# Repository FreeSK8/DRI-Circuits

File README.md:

# DRI-Circuits
Derelict Robot Industries Sandbox of various OS schematics &amp; board design files.

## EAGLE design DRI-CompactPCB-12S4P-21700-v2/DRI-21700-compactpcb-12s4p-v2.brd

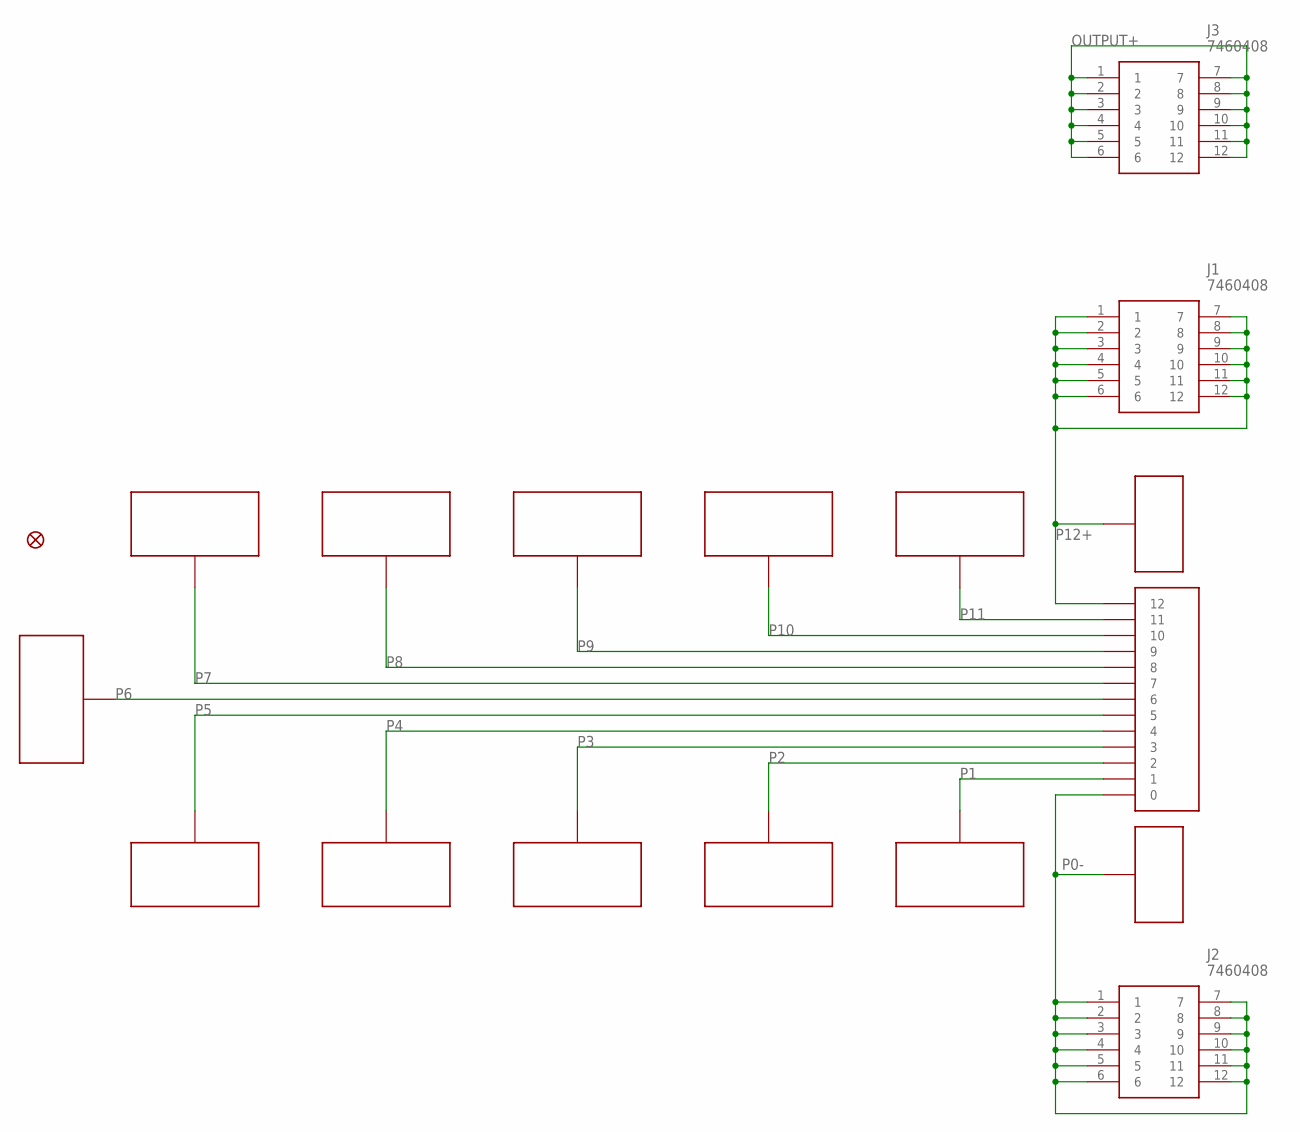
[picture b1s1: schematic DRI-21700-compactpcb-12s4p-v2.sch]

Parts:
FD2: FIDUCIAL1X2; FIDUCIAL-1X2
J1, J2, J3: 7460408
JP1: 13P-JST-2MM
P0: BUS-TERM-PAD-; TERM-PAD-
P1, P2, P3, P4, P5, P7, P8, P9, P10, P11: BAT-TERM-L
P6: BAT-TERM-END
P12: BUS-TERM-PAD+; TERM-PAD-

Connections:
OUTPUT+: J3.1, J3.2, J3.3, J3.4, J3.5, J3.6, J3.7, J3.8, J3.9, J3.10, J3.11, J3.12
P0-: J2.1, J2.2, J2.3, J2.4, J2.5, J2.6, J2.7, J2.8, J2.9, J2.10, J2.11, J2.12, JP1.P$1 (0), P0.P$3, P0.P$4, P0.P$5, P0.P$6, P0.P$7, P0.P$8, P0.P$9, P0.P$10, P0.P$11, P0.P$12, P0.P$13, P0.P$14, P0.P$15, P0.P$16, P0.P$17, P0.P$18, P0.P$19, P0.P$20, P0.P$21, P0.P$22, P0.P$23, P0.P$24, P0.P$25, P0.P$26, P0.P$27, P0.P$28, P0.P$29, P0.P$30, P0.P$31, P0.P$32, P0.P$33, P0.P$34, P0.P$35, P0.P$36, P0.P$37, P0.P$38, P0.P$39, P0.P$40, P0.P$41, P0.P$42, P0.P$43, P0.P$44, P0.P$45, P0.P$46, P0.P$47, P0.P$48, P0.P$49, P0.P$50, P0.P$51, P0.P$52, P0.P$53, P0.P$54, P0.P$55, P0.P$56, P0.P$57, P0.P$58, P0.P$59, P0.P$60, P0.P$61, P0.P$62, P0.P$63, P0.P$64, P0.P$65, P0.P$66, P0.P$67, P0.P$68, P0.P$69, P0.P$70, P0.P$71, P0.P$72, P0.P$73, P0.P$74, P0.P$75, P0.P$76, P0.P$77, P0.P$78, P0.P$79, P0.P$80, P0.P$81, P0.P$82, P0.P$83, P0.P$84, P0.P$85, P0.P$86, P0.P$87, P0.P$88, P0.P$89, P0.P$90, P0.P$91, P0.P$92, P0.P$93, P0.P$94, P0.P$95, P0.P$96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
P1: JP1.P$2 (1), P1.P$1, P1.P$2, P1.P$3, P1.P$4, P1.P$5, P1.P$6, P1.P$7, P1.P$8, P1.P$9, P1.P$10, P1.P$11, P1.P$12, P1.P$13, P1.P$14, P1.P$15, P1.P$16, P1.P$17, P1.P$18, P1.P$19, P1.P$20, P1.P$21, P1.P$22, P1.P$23, P1.P$24, P1.P$25, P1.P$26, P1.P$27, P1.P$28, P1.P$29, P1.P$30, P1.P$31, P1.P$32, P1.P$33, P1.P$34, P1.P$35, P1.P$36, P1.P$37, P1.P$38, P1.P$39, P1.P$40, P1.P$41, P1.P$42, P1.P$43, P1.P$44, P1.P$45, P1.P$46, P1.P$47, P1.P$48, P1.P$49, P1.P$50, P1.P$51, P1.P$52, P1.P$53, P1.P$54, P1.P$55, P1.P$56, P1.P$57, P1.P$58, P1.P$59, P1.P$60, P1.P$61, P1.P$62, P1.P$63, P1.P$64, P1.P$65, P1.P$66, P1.P$67, P1.P$68, P1.P$69, P1.P$70, P1.P$71, P1.P$72, P1.P$73, P1.P$74, P1.P$75, P1.P$76, P1.P$77, P1.P$78, P1.P$79, P1.P$80, P1.P$81, P1.P$82, P1.P$83, P1.P$84, P1.P$85, P1.P$86, P1.P$87, P1.P$88, P1.P$89, P1.P$90, P1.P$91, P1.P$92, P1.P$93, P1.P$94, P1.P$95, P1.P$96, P1.P$97, P1.P$98, P1.P$99, P1.P$100, P1.P$101, P1.P$102, P1.P$103, P1.P$104, P1.P$105, P1.P$106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
P2: JP1.P$3 (2), P2.P$1, P2.P$2, P2.P$3, P2.P$4, P2.P$5, P2.P$6, P2.P$7, P2.P$8, P2.P$9, P2.P$10, P2.P$11, P2.P$12, P2.P$13, P2.P$14, P2.P$15, P2.P$16, P2.P$17, P2.P$18, P2.P$19, P2.P$20, P2.P$21, P2.P$22, P2.P$23, P2.P$24, P2.P$25, P2.P$26, P2.P$27, P2.P$28, P2.P$29, P2.P$30, P2.P$31, P2.P$32, P2.P$33, P2.P$34, P2.P$35, P2.P$36, P2.P$37, P2.P$38, P2.P$39, P2.P$40, P2.P$41, P2.P$42, P2.P$43, P2.P$44, P2.P$45, P2.P$46, P2.P$47, P2.P$48, P2.P$49, P2.P$50, P2.P$51, P2.P$52, P2.P$53, P2.P$54, P2.P$55, P2.P$56, P2.P$57, P2.P$58, P2.P$59, P2.P$60, P2.P$61, P2.P$62, P2.P$63, P2.P$64, P2.P$65, P2.P$66, P2.P$67, P2.P$68, P2.P$69, P2.P$70, P2.P$71, P2.P$72, P2.P$73, P2.P$74, P2.P$75, P2.P$76, P2.P$77, P2.P$78, P2.P$79, P2.P$80, P2.P$81, P2.P$82, P2.P$83, P2.P$84, P2.P$85, P2.P$86, P2.P$87, P2.P$88, P2.P$89, P2.P$90, P2.P$91, P2.P$92, P2.P$93, P2.P$94, P2.P$95, P2.P$96, P2.P$97, P2.P$98, P2.P$99, P2.P$100, P2.P$101, P2.P$102, P2.P$103, P2.P$104, P2.P$105, P2.P$106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
P3: JP1.P$4 (3), P3.P$1, P3.P$2, P3.P$3, P3.P$4, P3.P$5, P3.P$6, P3.P$7, P3.P$8, P3.P$9, P3.P$10, P3.P$11, P3.P$12, P3.P$13, P3.P$14, P3.P$15, P3.P$16, P3.P$17, P3.P$18, P3.P$19, P3.P$20, P3.P$21, P3.P$22, P3.P$23, P3.P$24, P3.P$25, P3.P$26, P3.P$27, P3.P$28, P3.P$29, P3.P$30, P3.P$31, P3.P$32, P3.P$33, P3.P$34, P3.P$35, P3.P$36, P3.P$37, P3.P$38, P3.P$39, P3.P$40, P3.P$41, P3.P$42, P3.P$43, P3.P$44, P3.P$45, P3.P$46, P3.P$47, P3.P$48, P3.P$49, P3.P$50, P3.P$51, P3.P$52, P3.P$53, P3.P$54, P3.P$55, P3.P$56, P3.P$57, P3.P$58, P3.P$59, P3.P$60, P3.P$61, P3.P$62, P3.P$63, P3.P$64, P3.P$65, P3.P$66, P3.P$67, P3.P$68, P3.P$69, P3.P$70, P3.P$71, P3.P$72, P3.P$73, P3.P$74, P3.P$75, P3.P$76, P3.P$77, P3.P$78, P3.P$79, P3.P$80, P3.P$81, P3.P$82, P3.P$83, P3.P$84, P3.P$85, P3.P$86, P3.P$87, P3.P$88, P3.P$89, P3.P$90, P3.P$91, P3.P$92, P3.P$93, P3.P$94, P3.P$95, P3.P$96, P3.P$97, P3.P$98, P3.P$99, P3.P$100, P3.P$101, P3.P$102, P3.P$103, P3.P$104, P3.P$105, P3.P$106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
P4: JP1.P$5 (4), P4.P$1, P4.P$2, P4.P$3, P4.P$4, P4.P$5, P4.P$6, P4.P$7, P4.P$8, P4.P$9, P4.P$10, P4.P$11, P4.P$12, P4.P$13, P4.P$14, P4.P$15, P4.P$16, P4.P$17, P4.P$18, P4.P$19, P4.P$20, P4.P$21, P4.P$22, P4.P$23, P4.P$24, P4.P$25, P4.P$26, P4.P$27, P4.P$28, P4.P$29, P4.P$30, P4.P$31, P4.P$32, P4.P$33, P4.P$34, P4.P$35, P4.P$36, P4.P$37, P4.P$38, P4.P$39, P4.P$40, P4.P$41, P4.P$42, P4.P$43, P4.P$44, P4.P$45, P4.P$46, P4.P$47, P4.P$48, P4.P$49, P4.P$50, P4.P$51, P4.P$52, P4.P$53, P4.P$54, P4.P$55, P4.P$56, P4.P$57, P4.P$58, P4.P$59, P4.P$60, P4.P$61, P4.P$62, P4.P$63, P4.P$64, P4.P$65, P4.P$66, P4.P$67, P4.P$68, P4.P$69, P4.P$70, P4.P$71, P4.P$72, P4.P$73, P4.P$74, P4.P$75, P4.P$76, P4.P$77, P4.P$78, P4.P$79, P4.P$80, P4.P$81, P4.P$82, P4.P$83, P4.P$84, P4.P$85, P4.P$86, P4.P$87, P4.P$88, P4.P$89, P4.P$90, P4.P$91, P4.P$92, P4.P$93, P4.P$94, P4.P$95, P4.P$96, P4.P$97, P4.P$98, P4.P$99, P4.P$100, P4.P$101, P4.P$102, P4.P$103, P4.P$104, P4.P$105, P4.P$106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
P5: JP1.P$6 (5), P5.P$1, P5.P$2, P5.P$3, P5.P$4, P5.P$5, P5.P$6, P5.P$7, P5.P$8, P5.P$9, P5.P$10, P5.P$11, P5.P$12, P5.P$13, P5.P$14, P5.P$15, P5.P$16, P5.P$17, P5.P$18, P5.P$19, P5.P$20, P5.P$21, P5.P$22, P5.P$23, P5.P$24, P5.P$25, P5.P$26, P5.P$27, P5.P$28, P5.P$29, P5.P$30, P5.P$31, P5.P$32, P5.P$33, P5.P$34, P5.P$35, P5.P$36, P5.P$37, P5.P$38, P5.P$39, P5.P$40, P5.P$41, P5.P$42, P5.P$43, P5.P$44, P5.P$45, P5.P$46, P5.P$47, P5.P$48, P5.P$49, P5.P$50, P5.P$51, P5.P$52, P5.P$53, P5.P$54, P5.P$55, P5.P$56, P5.P$57, P5.P$58, P5.P$59, P5.P$60, P5.P$61, P5.P$62, P5.P$63, P5.P$64, P5.P$65, P5.P$66, P5.P$67, P5.P$68, P5.P$69, P5.P$70, P5.P$71, P5.P$72, P5.P$73, P5.P$74, P5.P$75, P5.P$76, P5.P$77, P5.P$78, P5.P$79, P5.P$80, P5.P$81, P5.P$82, P5.P$83, P5.P$84, P5.P$85, P5.P$86, P5.P$87, P5.P$88, P5.P$89, P5.P$90, P5.P$91, P5.P$92, P5.P$93, P5.P$94, P5.P$95, P5.P$96, P5.P$97, P5.P$98, P5.P$99, P5.P$100, P5.P$101, P5.P$102, P5.P$103, P5.P$104, P5.P$105, P5.P$106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
P6: JP1.P$7 (6), P6.P$1, P6.P$2, P6.P$3, P6.P$4, P6.P$5, P6.P$6, P6.P$7, P6.P$8, P6.P$9, P6.P$10, P6.P$11, P6.P$12, P6.P$13, P6.P$14, P6.P$15, P6.P$16, P6.P$17, P6.P$18, P6.P$19, P6.P$20, P6.P$21, P6.P$22, P6.P$23, P6.P$24, P6.P$25, P6.P$26, P6.P$27, P6.P$28, P6.P$29, P6.P$30, P6.P$31, P6.P$32, P6.P$33, P6.P$34, P6.P$35, P6.P$36, P6.P$37, P6.P$38, P6.P$39, P6.P$40, P6.P$41, P6.P$42, P6.P$43, P6.P$44, P6.P$45, P6.P$46, P6.P$47, P6.P$48, P6.P$49, P6.P$50, P6.P$51, P6.P$52, P6.P$53, P6.P$54, P6.P$55, P6.P$56, P6.P$57, P6.P$58, P6.P$59, P6.P$60, P6.P$61, P6.P$62, P6.P$63, P6.P$64, P6.P$65, P6.P$66, P6.P$67, P6.P$68, P6.P$69, P6.P$70, P6.P$71, P6.P$72, P6.P$73, P6.P$74, P6.P$75, P6.P$76, P6.P$77, P6.P$78, P6.P$79, P6.P$80, P6.P$81, P6.P$82, P6.P$83, P6.P$84, P6.P$85, P6.P$86, P6.P$87, P6.P$88, P6.P$89, P6.P$90, P6.P$91, P6.P$92, P6.P$93, P6.P$94, P6.P$95, P6.P$96, P6.P$97, P6.P$98, P6.P$99, P6.P$100, P6.P$101, P6.P$102, P6.P$103, P6.P$104, P6.P$105, P6.P$106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
P7: JP1.P$8 (7), P7.P$1, P7.P$2, P7.P$3, P7.P$4, P7.P$5, P7.P$6, P7.P$7, P7.P$8, P7.P$9, P7.P$10, P7.P$11, P7.P$12, P7.P$13, P7.P$14, P7.P$15, P7.P$16, P7.P$17, P7.P$18, P7.P$19, P7.P$20, P7.P$21, P7.P$22, P7.P$23, P7.P$24, P7.P$25, P7.P$26, P7.P$27, P7.P$28, P7.P$29, P7.P$30, P7.P$31, P7.P$32, P7.P$33, P7.P$34, P7.P$35, P7.P$36, P7.P$37, P7.P$38, P7.P$39, P7.P$40, P7.P$41, P7.P$42, P7.P$43, P7.P$44, P7.P$45, P7.P$46, P7.P$47, P7.P$48, P7.P$49, P7.P$50, P7.P$51, P7.P$52, P7.P$53, P7.P$54, P7.P$55, P7.P$56, P7.P$57, P7.P$58, P7.P$59, P7.P$60, P7.P$61, P7.P$62, P7.P$63, P7.P$64, P7.P$65, P7.P$66, P7.P$67, P7.P$68, P7.P$69, P7.P$70, P7.P$71, P7.P$72, P7.P$73, P7.P$74, P7.P$75, P7.P$76, P7.P$77, P7.P$78, P7.P$79, P7.P$80, P7.P$81, P7.P$82, P7.P$83, P7.P$84, P7.P$85, P7.P$86, P7.P$87, P7.P$88, P7.P$89, P7.P$90, P7.P$91, P7.P$92, P7.P$93, P7.P$94, P7.P$95, P7.P$96, P7.P$97, P7.P$98, P7.P$99, P7.P$100, P7.P$101, P7.P$102, P7.P$103, P7.P$104, P7.P$105, P7.P$106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
P8: JP1.P$9 (8), P8.P$1, P8.P$2, P8.P$3, P8.P$4, P8.P$5, P8.P$6, P8.P$7, P8.P$8, P8.P$9, P8.P$10, P8.P$11, P8.P$12, P8.P$13, P8.P$14, P8.P$15, P8.P$16, P8.P$17, P8.P$18, P8.P$19, P8.P$20, P8.P$21, P8.P$22, P8.P$23, P8.P$24, P8.P$25, P8.P$26, P8.P$27, P8.P$28, P8.P$29, P8.P$30, P8.P$31, P8.P$32, P8.P$33, P8.P$34, P8.P$35, P8.P$36, P8.P$37, P8.P$38, P8.P$39, P8.P$40, P8.P$41, P8.P$42, P8.P$43, P8.P$44, P8.P$45, P8.P$46, P8.P$47, P8.P$48, P8.P$49, P8.P$50, P8.P$51, P8.P$52, P8.P$53, P8.P$54, P8.P$55, P8.P$56, P8.P$57, P8.P$58, P8.P$59, P8.P$60, P8.P$61, P8.P$62, P8.P$63, P8.P$64, P8.P$65, P8.P$66, P8.P$67, P8.P$68, P8.P$69, P8.P$70, P8.P$71, P8.P$72, P8.P$73, P8.P$74, P8.P$75, P8.P$76, P8.P$77, P8.P$78, P8.P$79, P8.P$80, P8.P$81, P8.P$82, P8.P$83, P8.P$84, P8.P$85, P8.P$86, P8.P$87, P8.P$88, P8.P$89, P8.P$90, P8.P$91, P8.P$92, P8.P$93, P8.P$94, P8.P$95, P8.P$96, P8.P$97, P8.P$98, P8.P$99, P8.P$100, P8.P$101, P8.P$102, P8.P$103, P8.P$104, P8.P$105, P8.P$106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
P9: JP1.P$10 (9), P9.P$1, P9.P$2, P9.P$3, P9.P$4, P9.P$5, P9.P$6, P9.P$7, P9.P$8, P9.P$9, P9.P$10, P9.P$11, P9.P$12, P9.P$13, P9.P$14, P9.P$15, P9.P$16, P9.P$17, P9.P$18, P9.P$19, P9.P$20, P9.P$21, P9.P$22, P9.P$23, P9.P$24, P9.P$25, P9.P$26, P9.P$27, P9.P$28, P9.P$29, P9.P$30, P9.P$31, P9.P$32, P9.P$33, P9.P$34, P9.P$35, P9.P$36, P9.P$37, P9.P$38, P9.P$39, P9.P$40, P9.P$41, P9.P$42, P9.P$43, P9.P$44, P9.P$45, P9.P$46, P9.P$47, P9.P$48, P9.P$49, P9.P$50, P9.P$51, P9.P$52, P9.P$53, P9.P$54, P9.P$55, P9.P$56, P9.P$57, P9.P$58, P9.P$59, P9.P$60, P9.P$61, P9.P$62, P9.P$63, P9.P$64, P9.P$65, P9.P$66, P9.P$67, P9.P$68, P9.P$69, P9.P$70, P9.P$71, P9.P$72, P9.P$73, P9.P$74, P9.P$75, P9.P$76, P9.P$77, P9.P$78, P9.P$79, P9.P$80, P9.P$81, P9.P$82, P9.P$83, P9.P$84, P9.P$85, P9.P$86, P9.P$87, P9.P$88, P9.P$89, P9.P$90, P9.P$91, P9.P$92, P9.P$93, P9.P$94, P9.P$95, P9.P$96, P9.P$97, P9.P$98, P9.P$99, P9.P$100, P9.P$101, P9.P$102, P9.P$103, P9.P$104, P9.P$105, P9.P$106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
P10: JP1.P$11 (10), P10.P$1, P10.P$2, P10.P$3, P10.P$4, P10.P$5, P10.P$6, P10.P$7, P10.P$8, P10.P$9, P10.P$10, P10.P$11, P10.P$12, P10.P$13, P10.P$14, P10.P$15, P10.P$16, P10.P$17, P10.P$18, P10.P$19, P10.P$20, P10.P$21, P10.P$22, P10.P$23, P10.P$24, P10.P$25, P10.P$26, P10.P$27, P10.P$28, P10.P$29, P10.P$30, P10.P$31, P10.P$32, P10.P$33, P10.P$34, P10.P$35, P10.P$36, P10.P$37, P10.P$38, P10.P$39, P10.P$40, P10.P$41, P10.P$42, P10.P$43, P10.P$44, P10.P$45, P10.P$46, P10.P$47, P10.P$48, P10.P$49, P10.P$50, P10.P$51, P10.P$52, P10.P$53, P10.P$54, P10.P$55, P10.P$56, P10.P$57, P10.P$58, P10.P$59, P10.P$60, P10.P$61, P10.P$62, P10.P$63, P10.P$64, P10.P$65, P10.P$66, P10.P$67, P10.P$68, P10.P$69, P10.P$70, P10.P$71, P10.P$72, P10.P$73, P10.P$74, P10.P$75, P10.P$76, P10.P$77, P10.P$78, P10.P$79, P10.P$80, P10.P$81, P10.P$82, P10.P$83, P10.P$84, P10.P$85, P10.P$86, P10.P$87, P10.P$88, P10.P$89, P10.P$90, P10.P$91, P10.P$92, P10.P$93, P10.P$94, P10.P$95, P10.P$96, P10.P$97, P10.P$98, P10.P$99, P10.P$100, P10.P$101, P10.P$102, P10.P$103, P10.P$104, P10.P$105, P10.P$106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
P11: JP1.P$12 (11), P11.P$1, P11.P$2, P11.P$3, P11.P$4, P11.P$5, P11.P$6, P11.P$7, P11.P$8, P11.P$9, P11.P$10, P11.P$11, P11.P$12, P11.P$13, P11.P$14, P11.P$15, P11.P$16, P11.P$17, P11.P$18, P11.P$19, P11.P$20, P11.P$21, P11.P$22, P11.P$23, P11.P$24, P11.P$25, P11.P$26, P11.P$27, P11.P$28, P11.P$29, P11.P$30, P11.P$31, P11.P$32, P11.P$33, P11.P$34, P11.P$35, P11.P$36, P11.P$37, P11.P$38, P11.P$39, P11.P$40, P11.P$41, P11.P$42, P11.P$43, P11.P$44, P11.P$45, P11.P$46, P11.P$47, P11.P$48, P11.P$49, P11.P$50, P11.P$51, P11.P$52, P11.P$53, P11.P$54, P11.P$55, P11.P$56, P11.P$57, P11.P$58, P11.P$59, P11.P$60, P11.P$61, P11.P$62, P11.P$63, P11.P$64, P11.P$65, P11.P$66, P11.P$67, P11.P$68, P11.P$69, P11.P$70, P11.P$71, P11.P$72, P11.P$73, P11.P$74, P11.P$75, P11.P$76, P11.P$77, P11.P$78, P11.P$79, P11.P$80, P11.P$81, P11.P$82, P11.P$83, P11.P$84, P11.P$85, P11.P$86, P11.P$87, P11.P$88, P11.P$89, P11.P$90, P11.P$91, P11.P$92, P11.P$93, P11.P$94, P11.P$95, P11.P$96, P11.P$97, P11.P$98, P11.P$99, P11.P$100, P11.P$101, P11.P$102, P11.P$103, P11.P$104, P11.P$105, P11.P$106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
P12+: J1.1, J1.2, J1.3, J1.4, J1.5, J1.6, J1.7, J1.8, J1.9, J1.10, J1.11, J1.12, JP1.P$13 (12), P12.P$3, P12.P$4, P12.P$5, P12.P$6, P12.P$7, P12.P$8, P12.P$9, P12.P$10, P12.P$11, P12.P$12, P12.P$13, P12.P$14, P12.P$15, P12.P$16, P12.P$17, P12.P$18, P12.P$19, P12.P$20, P12.P$21, P12.P$22, P12.P$23, P12.P$24, P12.P$25, P12.P$26, P12.P$27, P12.P$28, P12.P$29, P12.P$30, P12.P$31, P12.P$32, P12.P$33, P12.P$34, P12.P$35, P12.P$36, P12.P$37, P12.P$38, P12.P$39, P12.P$40, P12.P$41, P12.P$42, P12.P$43, P12.P$44, P12.P$45, P12.P$46, P12.P$47, P12.P$48, P12.P$49, P12.P$50, P12.P$51, P12.P$52, P12.P$53, P12.P$54, P12.P$55, P12.P$56, P12.P$57, P12.P$58, P12.P$59, P12.P$60, P12.P$61, P12.P$62, P12.P$63, P12.P$64, P12.P$65, P12.P$66, P12.P$67, P12.P$68, P12.P$69, P12.P$70, P12.P$71, P12.P$72, P12.P$73, P12.P$74, P12.P$75, P12.P$76, P12.P$77, P12.P$78, P12.P$79, P12.P$80, P12.P$81, P12.P$82, P12.P$83, P12.P$84, P12.P$85, P12.P$86, P12.P$87, P12.P$88, P12.P$89, P12.P$90, P12.P$91, P12.P$92, P12.P$93, P12.P$94, P12.P$95, P12.P$96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

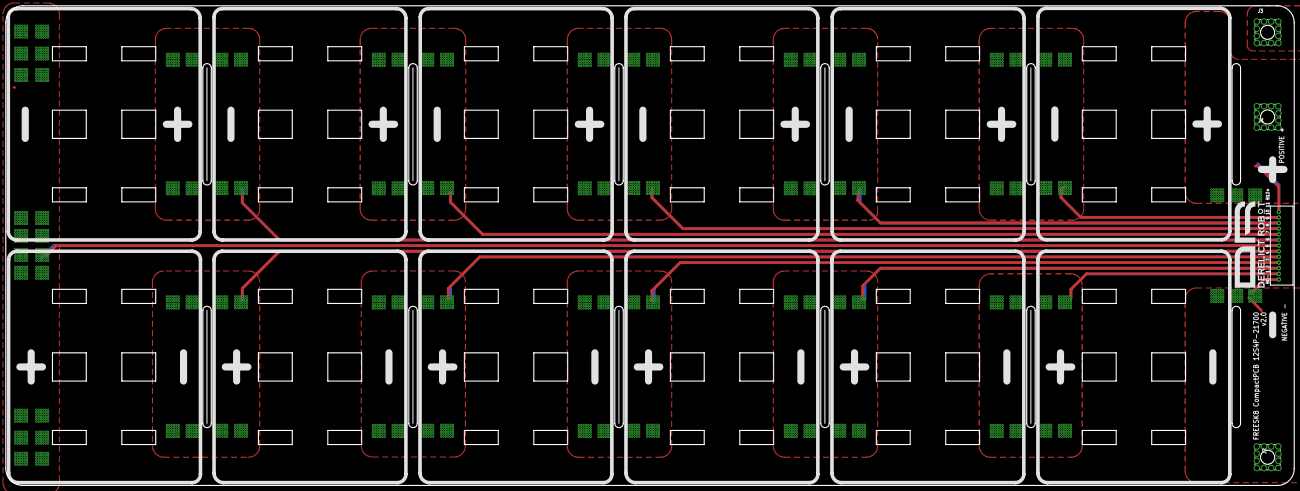
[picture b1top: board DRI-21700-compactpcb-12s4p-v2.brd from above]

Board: 2 copper layers, 456.6 x 170.0 mm, 30 parts (1 on the bottom side), 14 nets.

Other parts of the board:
U$1, U$2, U$3, U$4, U$5, U$6, U$7, U$8, U$9, U$10, U$11, U$12: 4PBATTERY

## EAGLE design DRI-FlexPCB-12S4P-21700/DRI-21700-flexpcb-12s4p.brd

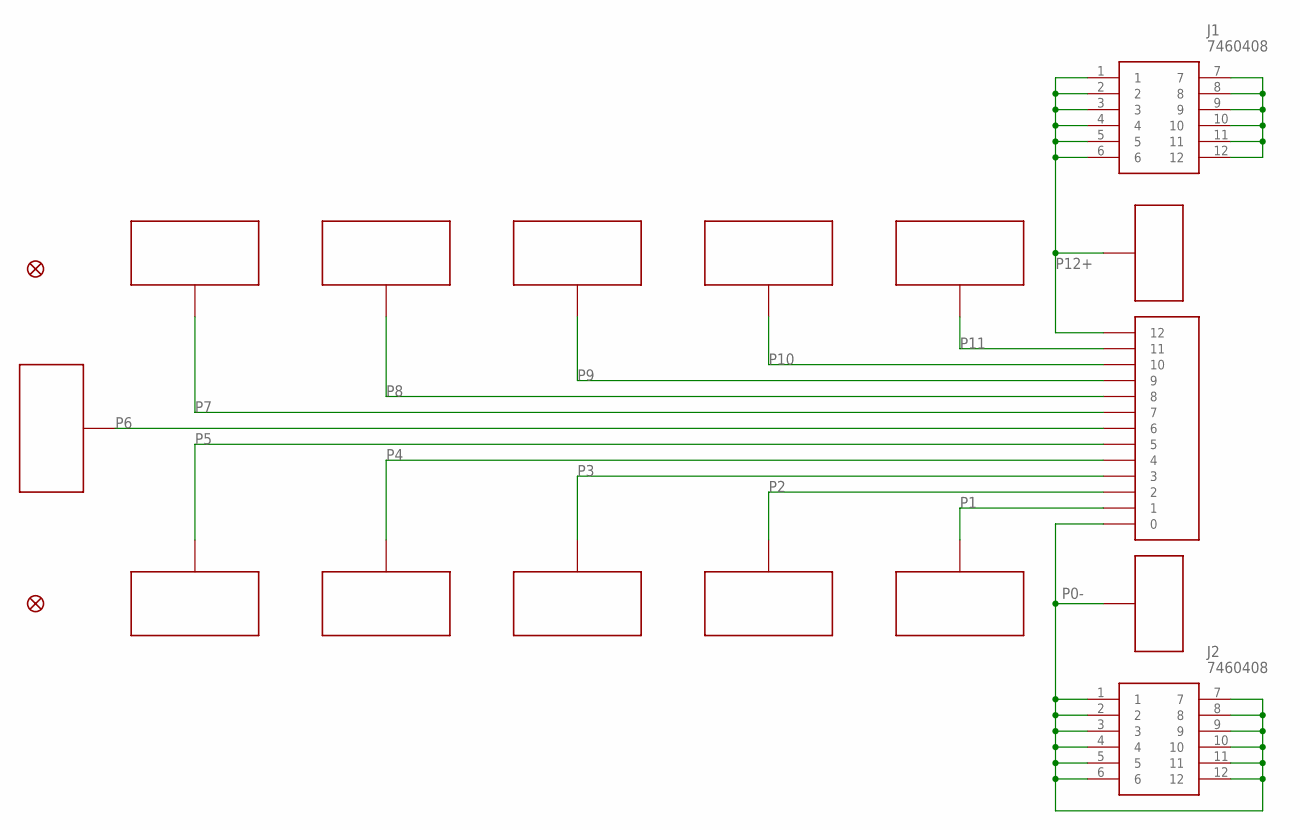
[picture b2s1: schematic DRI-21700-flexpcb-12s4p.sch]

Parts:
FD1, FD2: FIDUCIAL1X2; FIDUCIAL-1X2
J1, J2: 7460408
JP1: 13P-JST-2MM
P0, P12: BUS-TERM-PAD+; TERM-PAD-
P1, P3, P5, P7, P9, P11: BAT-TERM-L
P2, P4, P8, P10: BAT-TERM-M
P6: BAT-TERM-END

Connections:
unnamed: J1.7, J1.8, J1.9, J1.10, J1.11, J1.12
P0-: J2.1, J2.2, J2.3, J2.4, J2.5, J2.6, J2.7, J2.8, J2.9, J2.10, J2.11, J2.12, JP1.P$1 (0), P0.P$3, P0.P$4, P0.P$5, P0.P$6, P0.P$7, P0.P$8, P0.P$9, P0.P$10, P0.P$11, P0.P$12, P0.P$13, P0.P$14, P0.P$15, P0.P$16, P0.P$17, P0.P$18, P0.P$19, P0.P$20, P0.P$21, P0.P$22, P0.P$23, P0.P$24, P0.P$25, P0.P$26, P0.P$27, P0.P$28, P0.P$29, P0.P$30, P0.P$31, P0.P$32, P0.P$33, P0.P$34, P0.P$35, P0.P$36, P0.P$37, P0.P$38, P0.P$39, P0.P$40, P0.P$41, P0.P$42, P0.P$43, P0.P$44, P0.P$45, P0.P$46, P0.P$47, P0.P$48, P0.P$49, P0.P$50, P0.P$51, P0.P$52, P0.P$53, P0.P$54, P0.P$55, P0.P$56, P0.P$57, P0.P$58, P0.P$59, P0.P$60, P0.P$61, P0.P$62, P0.P$63, P0.P$64, P0.P$65, P0.P$66, P0.P$67, P0.P$68, P0.P$69, P0.P$70, P0.P$71, P0.P$72, P0.P$73, P0.P$74, P0.P$75, P0.P$76, P0.P$77, P0.P$78, P0.P$79, P0.P$80, P0.P$81, P0.P$82, P0.P$83, P0.P$84, P0.P$85, P0.P$86, P0.P$87, P0.P$88, P0.P$89, P0.P$90, P0.P$91, P0.P$92, P0.P$93, P0.P$94, P0.P$95, P0.P$96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
P1: JP1.P$2 (1), P1.P$5, P1.P$6, P1.P$7, P1.P$8, P1.P$9, P1.P$10, P1.P$11, P1.P$12, P1.P$13, P1.P$14, P1.P$15, P1.P$16, P1.P$17, P1.P$18, P1.P$19, P1.P$20, P1.P$21, P1.P$22, P1.P$23, P1.P$24, P1.P$25, P1.P$26, P1.P$27, P1.P$28, P1.P$29, P1.P$30, P1.P$31, P1.P$32, P1.P$33, P1.P$34, P1.P$35, P1.P$36, P1.P$37, P1.P$38, P1.P$39, P1.P$40, P1.P$41, P1.P$42, P1.P$43, P1.P$44, P1.P$45, P1.P$46, P1.P$47, P1.P$48, P1.P$49, P1.P$50, P1.P$51, P1.P$52, P1.P$53, P1.P$54, P1.P$55, P1.P$56, P1.P$57, P1.P$58, P1.P$59, P1.P$60, P1.P$61, P1.P$62, P1.P$63, P1.P$64, P1.P$65, P1.P$66, P1.P$67, P1.P$68, P1.P$69, P1.P$70, P1.P$71, P1.P$72, P1.P$73, P1.P$74, P1.P$75, P1.P$76, P1.P$77, P1.P$78, P1.P$79, P1.P$80, P1.P$81, P1.P$82, P1.P$83, P1.P$84, P1.P$85, P1.P$86, P1.P$87, P1.P$88, P1.P$89, P1.P$90, P1.P$91, P1.P$92, P1.P$93, P1.P$94, P1.P$95, P1.P$96, P1.P$97, P1.P$98, P1.P$99, P1.P$100, P1.P$101, P1.P$102, P1.P$103, P1.P$104, P1.P$105, P1.P$106, P1.P$107, P1.P$108, P1.P$109, P1.P$110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
P2: JP1.P$3 (2), P2.P$5, P2.P$6, P2.P$7, P2.P$8, P2.P$9, P2.P$10, P2.P$11, P2.P$12, P2.P$13, P2.P$14, P2.P$15, P2.P$16, P2.P$17, P2.P$18, P2.P$19, P2.P$20, P2.P$21, P2.P$22, P2.P$23, P2.P$24, P2.P$25, P2.P$26, P2.P$27, P2.P$28, P2.P$29, P2.P$30, P2.P$31, P2.P$32, P2.P$33, P2.P$34, P2.P$35, P2.P$36, P2.P$37, P2.P$38, P2.P$39, P2.P$40, P2.P$42, P2.P$43, P2.P$44, P2.P$45, P2.P$46, P2.P$47, P2.P$48, P2.P$49, P2.P$50, P2.P$51, P2.P$52, P2.P$53, P2.P$54, P2.P$55, P2.P$56, P2.P$57, P2.P$58, P2.P$59, P2.P$60, P2.P$61, P2.P$62, P2.P$63, P2.P$64, P2.P$65, P2.P$66, P2.P$67, P2.P$68, P2.P$69, P2.P$70, P2.P$71, P2.P$72, P2.P$73, P2.P$74, P2.P$75, P2.P$76, P2.P$77, P2.P$79, P2.P$80, P2.P$81, P2.P$82, P2.P$83, P2.P$84, P2.P$85, P2.P$86, P2.P$87, P2.P$88, P2.P$89, P2.P$90, P2.P$91, P2.P$92, P2.P$93, P2.P$94, P2.P$95, P2.P$96, P2.P$97, P2.P$98, P2.P$99, P2.P$100, P2.P$101, P2.P$102, P2.P$103, P2.P$104, P2.P$105, P2.P$106, P2.P$107, P2.P$108, P2.P$109, P2.P$110, P2.P$111, P2.P$112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
P3: JP1.P$4 (3), P3.P$5, P3.P$6, P3.P$7, P3.P$8, P3.P$9, P3.P$10, P3.P$11, P3.P$12, P3.P$13, P3.P$14, P3.P$15, P3.P$16, P3.P$17, P3.P$18, P3.P$19, P3.P$20, P3.P$21, P3.P$22, P3.P$23, P3.P$24, P3.P$25, P3.P$26, P3.P$27, P3.P$28, P3.P$29, P3.P$30, P3.P$31, P3.P$32, P3.P$33, P3.P$34, P3.P$35, P3.P$36, P3.P$37, P3.P$38, P3.P$39, P3.P$40, P3.P$41, P3.P$42, P3.P$43, P3.P$44, P3.P$45, P3.P$46, P3.P$47, P3.P$48, P3.P$49, P3.P$50, P3.P$51, P3.P$52, P3.P$53, P3.P$54, P3.P$55, P3.P$56, P3.P$57, P3.P$58, P3.P$59, P3.P$60, P3.P$61, P3.P$62, P3.P$63, P3.P$64, P3.P$65, P3.P$66, P3.P$67, P3.P$68, P3.P$69, P3.P$70, P3.P$71, P3.P$72, P3.P$73, P3.P$74, P3.P$75, P3.P$76, P3.P$77, P3.P$78, P3.P$79, P3.P$80, P3.P$81, P3.P$82, P3.P$83, P3.P$84, P3.P$85, P3.P$86, P3.P$87, P3.P$88, P3.P$89, P3.P$90, P3.P$91, P3.P$92, P3.P$93, P3.P$94, P3.P$95, P3.P$96, P3.P$97, P3.P$98, P3.P$99, P3.P$100, P3.P$101, P3.P$102, P3.P$103, P3.P$104, P3.P$105, P3.P$106, P3.P$107, P3.P$108, P3.P$109, P3.P$110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
P4: JP1.P$5 (4), P4.P$5, P4.P$6, P4.P$7, P4.P$8, P4.P$9, P4.P$10, P4.P$11, P4.P$12, P4.P$13, P4.P$14, P4.P$15, P4.P$16, P4.P$17, P4.P$18, P4.P$19, P4.P$20, P4.P$21, P4.P$22, P4.P$23, P4.P$24, P4.P$25, P4.P$26, P4.P$27, P4.P$28, P4.P$29, P4.P$30, P4.P$31, P4.P$32, P4.P$33, P4.P$34, P4.P$35, P4.P$36, P4.P$37, P4.P$38, P4.P$39, P4.P$40, P4.P$42, P4.P$43, P4.P$44, P4.P$45, P4.P$46, P4.P$47, P4.P$48, P4.P$49, P4.P$50, P4.P$51, P4.P$52, P4.P$53, P4.P$54, P4.P$55, P4.P$56, P4.P$57, P4.P$58, P4.P$59, P4.P$60, P4.P$61, P4.P$62, P4.P$63, P4.P$64, P4.P$65, P4.P$66, P4.P$67, P4.P$68, P4.P$69, P4.P$70, P4.P$71, P4.P$72, P4.P$73, P4.P$74, P4.P$75, P4.P$76, P4.P$77, P4.P$79, P4.P$80, P4.P$81, P4.P$82, P4.P$83, P4.P$84, P4.P$85, P4.P$86, P4.P$87, P4.P$88, P4.P$89, P4.P$90, P4.P$91, P4.P$92, P4.P$93, P4.P$94, P4.P$95, P4.P$96, P4.P$97, P4.P$98, P4.P$99, P4.P$100, P4.P$101, P4.P$102, P4.P$103, P4.P$104, P4.P$105, P4.P$106, P4.P$107, P4.P$108, P4.P$109, P4.P$110, P4.P$111, P4.P$112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
P5: JP1.P$6 (5), P5.P$5, P5.P$6, P5.P$7, P5.P$8, P5.P$9, P5.P$10, P5.P$11, P5.P$12, P5.P$13, P5.P$14, P5.P$15, P5.P$16, P5.P$17, P5.P$18, P5.P$19, P5.P$20, P5.P$21, P5.P$22, P5.P$23, P5.P$24, P5.P$25, P5.P$26, P5.P$27, P5.P$28, P5.P$29, P5.P$30, P5.P$31, P5.P$32, P5.P$33, P5.P$34, P5.P$35, P5.P$36, P5.P$37, P5.P$38, P5.P$39, P5.P$40, P5.P$41, P5.P$42, P5.P$43, P5.P$44, P5.P$45, P5.P$46, P5.P$47, P5.P$48, P5.P$49, P5.P$50, P5.P$51, P5.P$52, P5.P$53, P5.P$54, P5.P$55, P5.P$56, P5.P$57, P5.P$58, P5.P$59, P5.P$60, P5.P$61, P5.P$62, P5.P$63, P5.P$64, P5.P$65, P5.P$66, P5.P$67, P5.P$68, P5.P$69, P5.P$70, P5.P$71, P5.P$72, P5.P$73, P5.P$74, P5.P$75, P5.P$76, P5.P$77, P5.P$78, P5.P$79, P5.P$80, P5.P$81, P5.P$82, P5.P$83, P5.P$84, P5.P$85, P5.P$86, P5.P$87, P5.P$88, P5.P$89, P5.P$90, P5.P$91, P5.P$92, P5.P$93, P5.P$94, P5.P$95, P5.P$96, P5.P$97, P5.P$98, P5.P$99, P5.P$100, P5.P$101, P5.P$102, P5.P$103, P5.P$104, P5.P$105, P5.P$106, P5.P$107, P5.P$108, P5.P$109, P5.P$110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
P6: JP1.P$7 (6), P6.P$2, P6.P$3, P6.P$4, P6.P$5, P6.P$6, P6.P$7, P6.P$8, P6.P$9, P6.P$10, P6.P$11, P6.P$12, P6.P$13, P6.P$14, P6.P$15, P6.P$16, P6.P$17, P6.P$18, P6.P$19, P6.P$20, P6.P$21, P6.P$22, P6.P$23, P6.P$24, P6.P$25, P6.P$26, P6.P$27, P6.P$28, P6.P$29, P6.P$30, P6.P$31, P6.P$32, P6.P$33, P6.P$34, P6.P$35, P6.P$36, P6.P$37, P6.P$39, P6.P$40, P6.P$41, P6.P$42, P6.P$43, P6.P$44, P6.P$45, P6.P$46, P6.P$47, P6.P$48, P6.P$49, P6.P$50, P6.P$51, P6.P$52, P6.P$53, P6.P$54, P6.P$55, P6.P$56, P6.P$57, P6.P$58, P6.P$59, P6.P$60, P6.P$61, P6.P$62, P6.P$63, P6.P$64, P6.P$65, P6.P$66, P6.P$67, P6.P$68, P6.P$69, P6.P$70, P6.P$71, P6.P$72, P6.P$73, P6.P$74, P6.P$76, P6.P$77, P6.P$78, P6.P$79, P6.P$80, P6.P$81, P6.P$82, P6.P$83, P6.P$84, P6.P$85, P6.P$86, P6.P$87, P6.P$88, P6.P$89, P6.P$90, P6.P$91, P6.P$92, P6.P$93, P6.P$94, P6.P$95, P6.P$96, P6.P$97, P6.P$98, P6.P$99, P6.P$100, P6.P$101, P6.P$102, P6.P$103, P6.P$104, P6.P$105, P6.P$106, P6.P$107, P6.P$108, P6.P$109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
P7: JP1.P$8 (7), P7.P$5, P7.P$6, P7.P$7, P7.P$8, P7.P$9, P7.P$10, P7.P$11, P7.P$12, P7.P$13, P7.P$14, P7.P$15, P7.P$16, P7.P$17, P7.P$18, P7.P$19, P7.P$20, P7.P$21, P7.P$22, P7.P$23, P7.P$24, P7.P$25, P7.P$26, P7.P$27, P7.P$28, P7.P$29, P7.P$30, P7.P$31, P7.P$32, P7.P$33, P7.P$34, P7.P$35, P7.P$36, P7.P$37, P7.P$38, P7.P$39, P7.P$40, P7.P$41, P7.P$42, P7.P$43, P7.P$44, P7.P$45, P7.P$46, P7.P$47, P7.P$48, P7.P$49, P7.P$50, P7.P$51, P7.P$52, P7.P$53, P7.P$54, P7.P$55, P7.P$56, P7.P$57, P7.P$58, P7.P$59, P7.P$60, P7.P$61, P7.P$62, P7.P$63, P7.P$64, P7.P$65, P7.P$66, P7.P$67, P7.P$68, P7.P$69, P7.P$70, P7.P$71, P7.P$72, P7.P$73, P7.P$74, P7.P$75, P7.P$76, P7.P$77, P7.P$78, P7.P$79, P7.P$80, P7.P$81, P7.P$82, P7.P$83, P7.P$84, P7.P$85, P7.P$86, P7.P$87, P7.P$88, P7.P$89, P7.P$90, P7.P$91, P7.P$92, P7.P$93, P7.P$94, P7.P$95, P7.P$96, P7.P$97, P7.P$98, P7.P$99, P7.P$100, P7.P$101, P7.P$102, P7.P$103, P7.P$104, P7.P$105, P7.P$106, P7.P$107, P7.P$108, P7.P$109, P7.P$110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
P8: JP1.P$9 (8), P8.P$5, P8.P$6, P8.P$7, P8.P$8, P8.P$9, P8.P$10, P8.P$11, P8.P$12, P8.P$13, P8.P$14, P8.P$15, P8.P$16, P8.P$17, P8.P$18, P8.P$19, P8.P$20, P8.P$21, P8.P$22, P8.P$23, P8.P$24, P8.P$25, P8.P$26, P8.P$27, P8.P$28, P8.P$29, P8.P$30, P8.P$31, P8.P$32, P8.P$33, P8.P$34, P8.P$35, P8.P$36, P8.P$37, P8.P$38, P8.P$39, P8.P$40, P8.P$42, P8.P$43, P8.P$44, P8.P$45, P8.P$46, P8.P$47, P8.P$48, P8.P$49, P8.P$50, P8.P$51, P8.P$52, P8.P$53, P8.P$54, P8.P$55, P8.P$56, P8.P$57, P8.P$58, P8.P$59, P8.P$60, P8.P$61, P8.P$62, P8.P$63, P8.P$64, P8.P$65, P8.P$66, P8.P$67, P8.P$68, P8.P$69, P8.P$70, P8.P$71, P8.P$72, P8.P$73, P8.P$74, P8.P$75, P8.P$76, P8.P$77, P8.P$79, P8.P$80, P8.P$81, P8.P$82, P8.P$83, P8.P$84, P8.P$85, P8.P$86, P8.P$87, P8.P$88, P8.P$89, P8.P$90, P8.P$91, P8.P$92, P8.P$93, P8.P$94, P8.P$95, P8.P$96, P8.P$97, P8.P$98, P8.P$99, P8.P$100, P8.P$101, P8.P$102, P8.P$103, P8.P$104, P8.P$105, P8.P$106, P8.P$107, P8.P$108, P8.P$109, P8.P$110, P8.P$111, P8.P$112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
P9: JP1.P$10 (9), P9.P$5, P9.P$6, P9.P$7, P9.P$8, P9.P$9, P9.P$10, P9.P$11, P9.P$12, P9.P$13, P9.P$14, P9.P$15, P9.P$16, P9.P$17, P9.P$18, P9.P$19, P9.P$20, P9.P$21, P9.P$22, P9.P$23, P9.P$24, P9.P$25, P9.P$26, P9.P$27, P9.P$28, P9.P$29, P9.P$30, P9.P$31, P9.P$32, P9.P$33, P9.P$34, P9.P$35, P9.P$36, P9.P$37, P9.P$38, P9.P$39, P9.P$40, P9.P$41, P9.P$42, P9.P$43, P9.P$44, P9.P$45, P9.P$46, P9.P$47, P9.P$48, P9.P$49, P9.P$50, P9.P$51, P9.P$52, P9.P$53, P9.P$54, P9.P$55, P9.P$56, P9.P$57, P9.P$58, P9.P$59, P9.P$60, P9.P$61, P9.P$62, P9.P$63, P9.P$64, P9.P$65, P9.P$66, P9.P$67, P9.P$68, P9.P$69, P9.P$70, P9.P$71, P9.P$72, P9.P$73, P9.P$74, P9.P$75, P9.P$76, P9.P$77, P9.P$78, P9.P$79, P9.P$80, P9.P$81, P9.P$82, P9.P$83, P9.P$84, P9.P$85, P9.P$86, P9.P$87, P9.P$88, P9.P$89, P9.P$90, P9.P$91, P9.P$92, P9.P$93, P9.P$94, P9.P$95, P9.P$96, P9.P$97, P9.P$98, P9.P$99, P9.P$100, P9.P$101, P9.P$102, P9.P$103, P9.P$104, P9.P$105, P9.P$106, P9.P$107, P9.P$108, P9.P$109, P9.P$110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
P10: JP1.P$11 (10), P10.P$5, P10.P$6, P10.P$7, P10.P$8, P10.P$9, P10.P$10, P10.P$11, P10.P$12, P10.P$13, P10.P$14, P10.P$15, P10.P$16, P10.P$17, P10.P$18, P10.P$19, P10.P$20, P10.P$21, P10.P$22, P10.P$23, P10.P$24, P10.P$25, P10.P$26, P10.P$27, P10.P$28, P10.P$29, P10.P$30, P10.P$31, P10.P$32, P10.P$33, P10.P$34, P10.P$35, P10.P$36, P10.P$37, P10.P$38, P10.P$39, P10.P$40, P10.P$42, P10.P$43, P10.P$44, P10.P$45, P10.P$46, P10.P$47, P10.P$48, P10.P$49, P10.P$50, P10.P$51, P10.P$52, P10.P$53, P10.P$54, P10.P$55, P10.P$56, P10.P$57, P10.P$58, P10.P$59, P10.P$60, P10.P$61, P10.P$62, P10.P$63, P10.P$64, P10.P$65, P10.P$66, P10.P$67, P10.P$68, P10.P$69, P10.P$70, P10.P$71, P10.P$72, P10.P$73, P10.P$74, P10.P$75, P10.P$76, P10.P$77, P10.P$79, P10.P$80, P10.P$81, P10.P$82, P10.P$83, P10.P$84, P10.P$85, P10.P$86, P10.P$87, P10.P$88, P10.P$89, P10.P$90, P10.P$91, P10.P$92, P10.P$93, P10.P$94, P10.P$95, P10.P$96, P10.P$97, P10.P$98, P10.P$99, P10.P$100, P10.P$101, P10.P$102, P10.P$103, P10.P$104, P10.P$105, P10.P$106, P10.P$107, P10.P$108, P10.P$109, P10.P$110, P10.P$111, P10.P$112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
P11: JP1.P$12 (11), P11.P$5, P11.P$6, P11.P$7, P11.P$8, P11.P$9, P11.P$10, P11.P$11, P11.P$12, P11.P$13, P11.P$14, P11.P$15, P11.P$16, P11.P$17, P11.P$18, P11.P$19, P11.P$20, P11.P$21, P11.P$22, P11.P$23, P11.P$24, P11.P$25, P11.P$26, P11.P$27, P11.P$28, P11.P$29, P11.P$30, P11.P$31, P11.P$32, P11.P$33, P11.P$34, P11.P$35, P11.P$36, P11.P$37, P11.P$38, P11.P$39, P11.P$40, P11.P$41, P11.P$42, P11.P$43, P11.P$44, P11.P$45, P11.P$46, P11.P$47, P11.P$48, P11.P$49, P11.P$50, P11.P$51, P11.P$52, P11.P$53, P11.P$54, P11.P$55, P11.P$56, P11.P$57, P11.P$58, P11.P$59, P11.P$60, P11.P$61, P11.P$62, P11.P$63, P11.P$64, P11.P$65, P11.P$66, P11.P$67, P11.P$68, P11.P$69, P11.P$70, P11.P$71, P11.P$72, P11.P$73, P11.P$74, P11.P$75, P11.P$76, P11.P$77, P11.P$78, P11.P$79, P11.P$80, P11.P$81, P11.P$82, P11.P$83, P11.P$84, P11.P$85, P11.P$86, P11.P$87, P11.P$88, P11.P$89, P11.P$90, P11.P$91, P11.P$92, P11.P$93, P11.P$94, P11.P$95, P11.P$96, P11.P$97, P11.P$98, P11.P$99, P11.P$100, P11.P$101, P11.P$102, P11.P$103, P11.P$104, P11.P$105, P11.P$106, P11.P$107, P11.P$108, P11.P$109, P11.P$110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
P12+: J1.1, J1.2, J1.3, J1.4, J1.5, J1.6, JP1.P$13 (12), P12.P$3, P12.P$4, P12.P$5, P12.P$6, P12.P$7, P12.P$8, P12.P$9, P12.P$10, P12.P$11, P12.P$12, P12.P$13, P12.P$14, P12.P$15, P12.P$16, P12.P$17, P12.P$18, P12.P$19, P12.P$20, P12.P$21, P12.P$22, P12.P$23, P12.P$24, P12.P$25, P12.P$26, P12.P$27, P12.P$28, P12.P$29, P12.P$30, P12.P$31, P12.P$32, P12.P$33, P12.P$34, P12.P$35, P12.P$36, P12.P$37, P12.P$38, P12.P$39, P12.P$40, P12.P$41, P12.P$42, P12.P$43, P12.P$44, P12.P$45, P12.P$46, P12.P$47, P12.P$48, P12.P$49, P12.P$50, P12.P$51, P12.P$52, P12.P$53, P12.P$54, P12.P$55, P12.P$56, P12.P$57, P12.P$58, P12.P$59, P12.P$60, P12.P$61, P12.P$62, P12.P$63, P12.P$64, P12.P$65, P12.P$66, P12.P$67, P12.P$68, P12.P$69, P12.P$70, P12.P$71, P12.P$72, P12.P$73, P12.P$74, P12.P$75, P12.P$76, P12.P$77, P12.P$78, P12.P$79, P12.P$80, P12.P$81, P12.P$82, P12.P$83, P12.P$84, P12.P$85, P12.P$86, P12.P$87, P12.P$88, P12.P$89, P12.P$90, P12.P$91, P12.P$92, P12.P$93, P12.P$94, P12.P$95, P12.P$96, P12.P$97, P12.P$98, P12.P$99, P12.P$100, P12.P$101, P12.P$102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

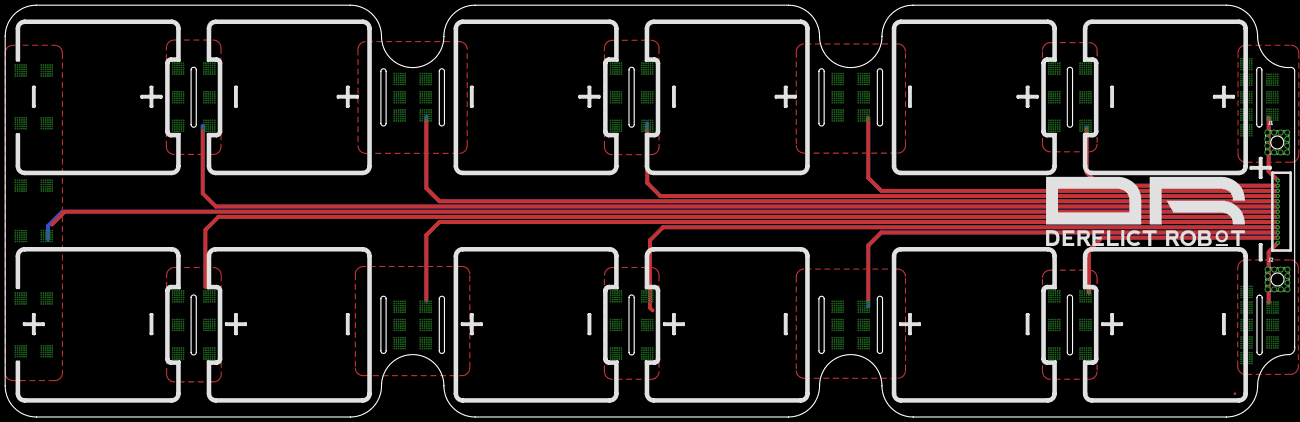
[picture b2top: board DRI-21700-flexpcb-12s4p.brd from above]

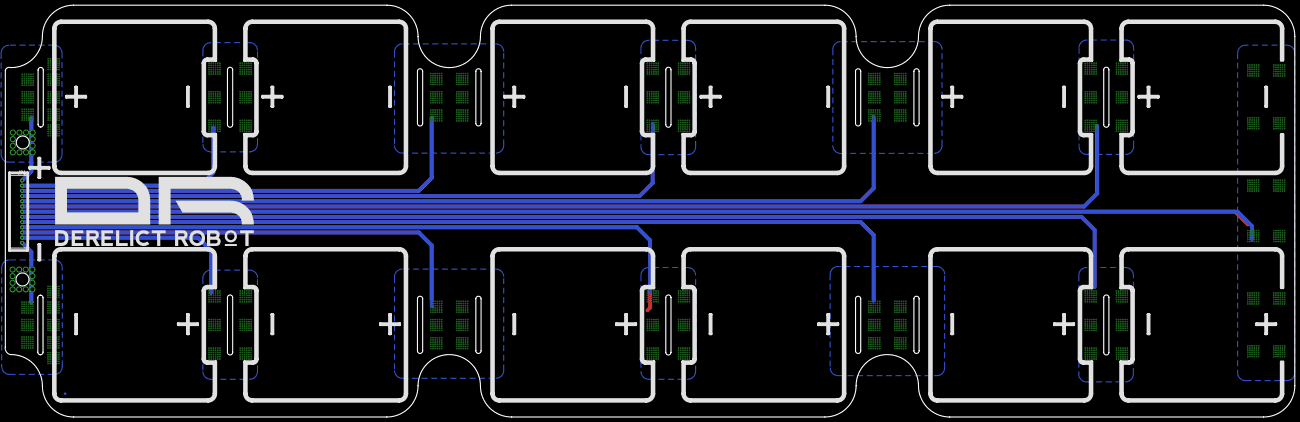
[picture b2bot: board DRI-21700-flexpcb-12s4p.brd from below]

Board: 2 copper layers, 496.0 x 158.4 mm, 18 parts (2 on the bottom side), 14 nets.

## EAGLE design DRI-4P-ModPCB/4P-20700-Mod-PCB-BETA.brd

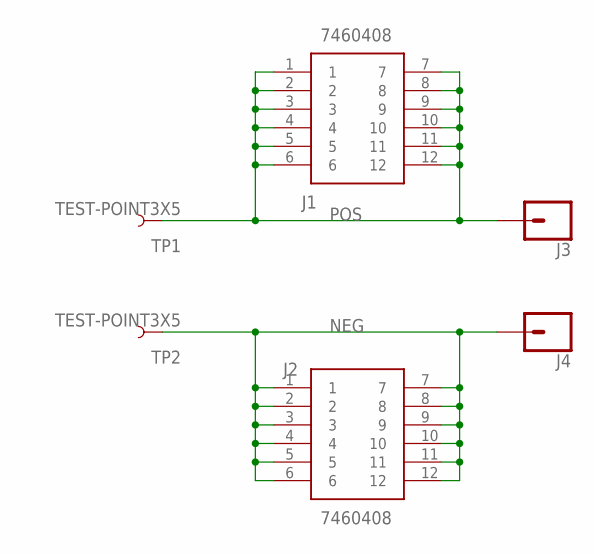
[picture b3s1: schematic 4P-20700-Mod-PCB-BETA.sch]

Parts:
J1, J2: 7460408
J3, J4: CONN_01; 1X01
TP1, TP2: TEST-POINT3X5; PAD.03X.05

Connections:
NEG: J2.1, J2.2, J2.3, J2.4, J2.5, J2.6, J2.7, J2.8, J2.9, J2.10, J2.11, J2.12, J4.1, TP2.P$1
POS: J1.1, J1.2, J1.3, J1.4, J1.5, J1.6, J1.7, J1.8, J1.9, J1.10, J1.11, J1.12, J3.1, TP1.P$1

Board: 2 copper layers, 6 parts (0 on the bottom side), 2 nets, no tracks yet.

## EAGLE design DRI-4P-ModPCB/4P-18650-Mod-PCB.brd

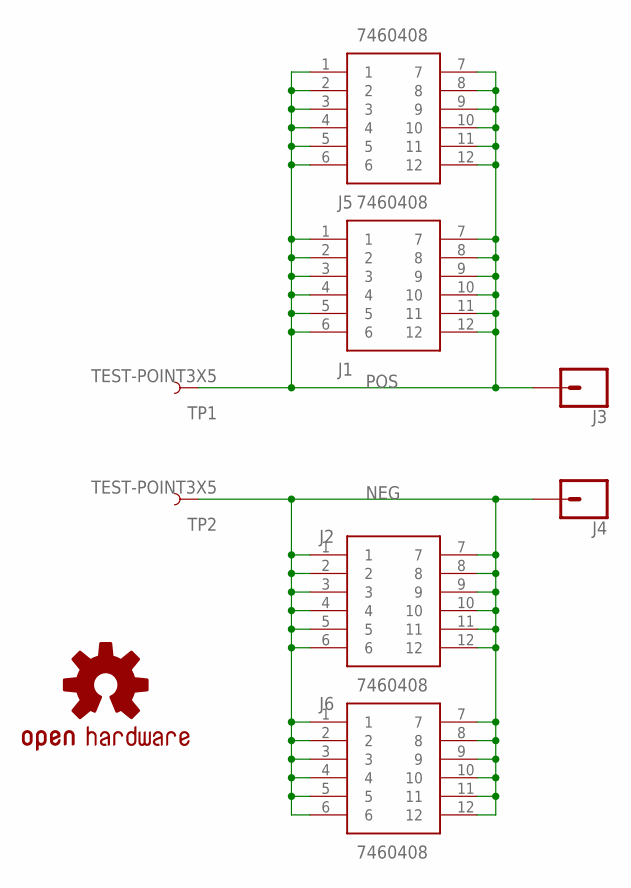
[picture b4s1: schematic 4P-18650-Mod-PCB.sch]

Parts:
J1, J2, J5, J6: 7460408
J3, J4: CONN_01; 1X01
LOGO1: OSHW-LOGOL; OSHW-LOGO-L
TP1, TP2: TEST-POINT3X5; PAD.03X.05

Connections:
NEG: J2.1, J2.2, J2.3, J2.4, J2.5, J2.6, J2.7, J2.8, J2.9, J2.10, J2.11, J2.12, J4.1, J6.1, J6.2, J6.3, J6.4, J6.5, J6.6, J6.7, J6.8, J6.9, J6.10, J6.11, J6.12, TP2.P$1
POS: J1.1, J1.2, J1.3, J1.4, J1.5, J1.6, J1.7, J1.8, J1.9, J1.10, J1.11, J1.12, J3.1, J5.1, J5.2, J5.3, J5.4, J5.5, J5.6, J5.7, J5.8, J5.9, J5.10, J5.11, J5.12, TP1.P$1

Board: 2 copper layers, 9 parts (0 on the bottom side), 2 nets, no tracks yet.

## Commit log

2020-05-09 Added 12S4P 18650 design files
2020-05-09 Added ModPCB
2020-05-09 Added 20700 beta 4p mod pcbs
2020-05-09 Added 5P 20700 Basic Battery PCB
2020-05-09 Added 5p18650 battery PCB - Skunk Edition
2020-06-15 Added Battery PCB variety pack!
2020-06-15 Add Compact PCB
2020-08-13 added 12s4p 21700 flexpcb design files
2020-10-01 Added 12S4P 21700 CompactPCB 2.0 EagleCAD Design files

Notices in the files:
parts and their libraries:
SparkFun-Connectors: Licensing: Creative Commons ShareAlike 4.0 International - https://creativecommons.org/licenses/by-sa/4.0
